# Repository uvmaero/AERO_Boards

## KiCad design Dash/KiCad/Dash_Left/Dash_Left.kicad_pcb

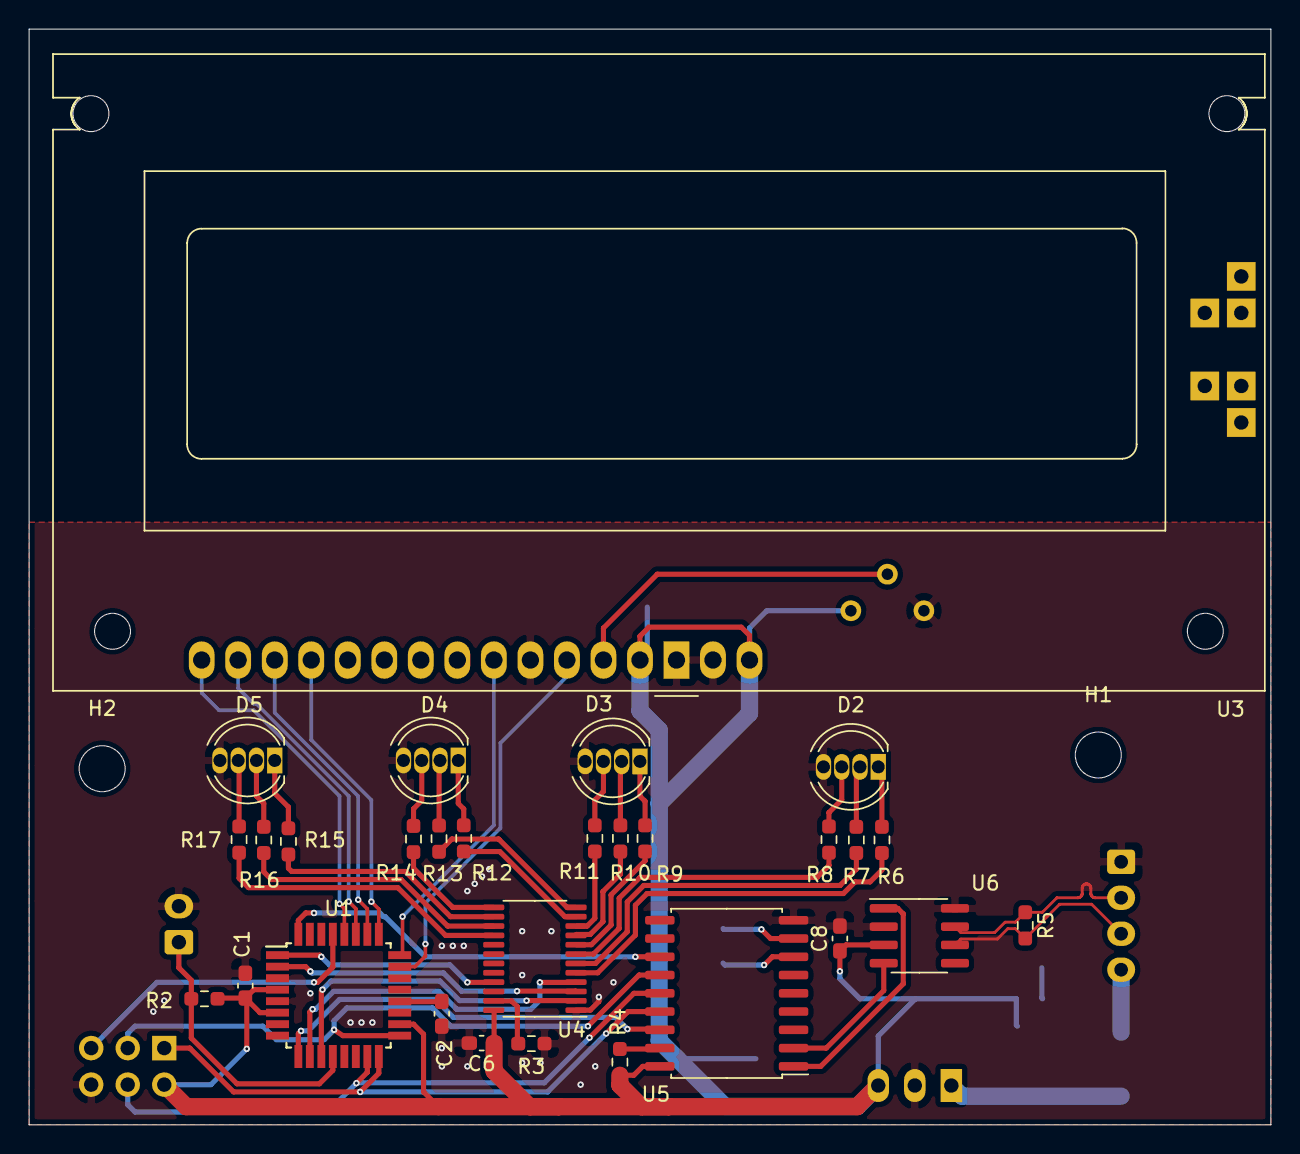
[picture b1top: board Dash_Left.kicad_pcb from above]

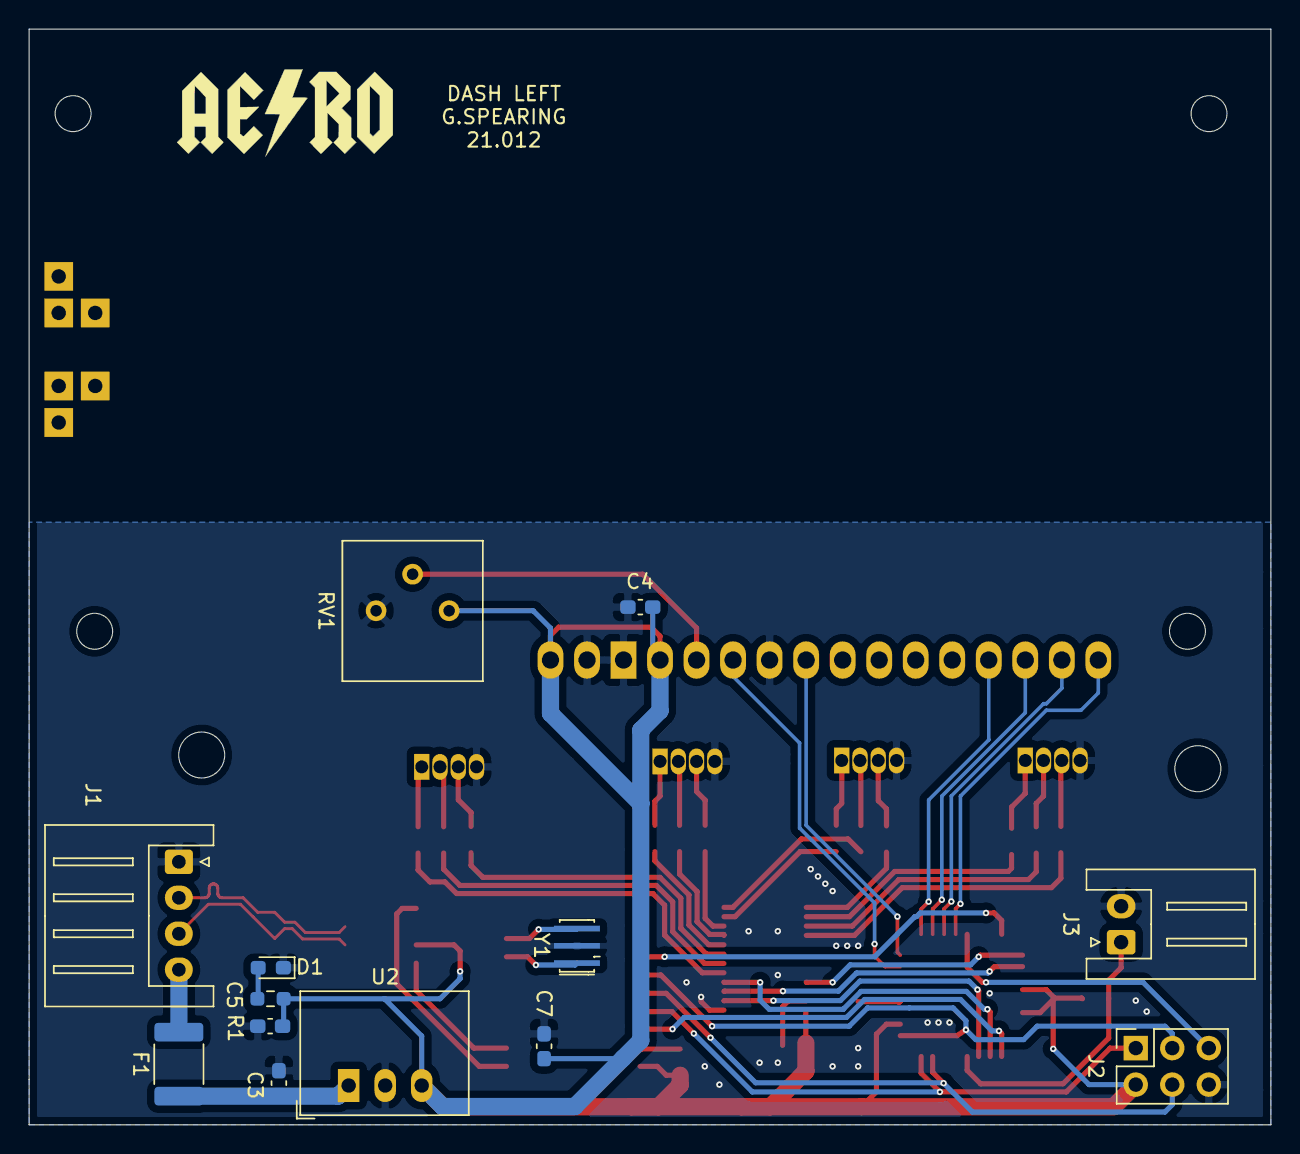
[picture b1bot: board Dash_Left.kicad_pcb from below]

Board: 2 copper layers, 86.4 x 76.2 mm, 44 parts (13 on the bottom side), 56 nets.

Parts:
C1, C2, C4, C6, C7, C8: 0.1u; C_0603_1608Metric_Pad1.08x0.95mm_HandSolder
C3: 1u; C_0603_1608Metric_Pad1.08x0.95mm_HandSolder
C5: 10u; C_0603_1608Metric_Pad1.08x0.95mm_HandSolder
D1: LED; LED_0603_1608Metric_Pad1.05x0.95mm_HandSolder
D2, D3, D4, D5: LED_RGBA; LED_D5.0mm-4_RGB
F1: MF-MSMF050; Fuse_1812_4532Metric_Pad1.30x3.40mm_HandSolder
H1, H2: MountingHole; MountingHole_3.2mm_M3
J1: Conn_01x04; JST_XH_S4B-XH-A_1x04_P2.50mm_Horizontal
J2: Conn_02x03_Odd_Even; PinSocket_2x03_P2.54mm_Vertical
J3: Conn_01x02; JST_XH_S2B-XH-A_1x02_P2.50mm_Horizontal
R1, R6, R7, R8, R9, R10, R11, R12, R13, R14, R15, R16, R17: 330; R_0603_1608Metric_Pad0.98x0.95mm_HandSolder
R2, R4: 10K; R_0603_1608Metric_Pad0.98x0.95mm_HandSolder
R3: 1K; R_0603_1608Metric_Pad0.98x0.95mm_HandSolder
R5: 120; R_0603_1608Metric_Pad0.98x0.95mm_HandSolder
RV1: 10K TRIM; Potentiometer_Bourns_3386P_Vertical
U1: ATmega328P-AU; TQFP-32_7x7mm_P0.8mm
U2: R-785.0-1.0; Converter_DCDC_RECOM_R-78E-0.5_THT
U3: RC1602A
U4: STP16CP05; TSSOP-24_4.4x7.8mm_P0.65mm
U5: MCP2515-xSO; SOIC-18W_7.5x11.6mm_P1.27mm
U6: MCP2551-I-SN; SOIC-8_3.9x4.9mm_P1.27mm
Y1: 16MHz; Resonator_SMD_muRata_CSTxExxV-3Pin_3.0x1.1mm_HandSoldering

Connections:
+5V: C1.1, C4.1, C5.1, C6.1, C7.1, C8.1, J2.2, R1.2, R2.1, R4.1, RV1.1, U1.4, U1.6, U1.18, U2.3, U3.2, U3.15, U4.24, U5.18, U6.3
+12V: F1.2, J1.4
/BATT_B: R17.2, U4.16
/BATT_G: R16.2, U4.15
/BATT_R: R15.2, U4.14
/CAN+: J1.2, R5.1, U6.7
/CAN-: J1.3, R5.2, U6.6
/CAN_CS: U1.9, U5.16
/CAN_INT: U1.32, U5.12
/CAN_Interface/RXCAN: U5.2, U6.4
/CAN_Interface/TXCAN: U5.1, U6.1
/LCD_BTN: J3.1, R2.2, U1.12
/LCD_D4: U1.25, U3.11
/LCD_D5: U1.26, U3.12
/LCD_D6: U1.27, U3.13
/LCD_D7: U1.28, U3.14
/LCD_EN: U1.24, U3.6
/LCD_RS: U1.23, U3.4
/LED_CLK: U1.2, U4.3
/LED_LE: U1.10, U4.4
/LED_OE: U1.1, U4.21
/LED_SDI: U1.11, U4.2
/MISO: J2.1, U1.16, U5.15
/MOSI: J2.4, U1.15, U5.14
/RESET: J2.5, U1.29
/SCK: J2.3, U1.17, U5.13
/TEMP_IND1B: R8.2, U4.7
/TEMP_IND1G: R7.2, U4.6
/TEMP_IND1R: R6.2, U4.5
/TEMP_IND2B: R11.2, U4.10
/TEMP_IND2G: R10.2, U4.9
/TEMP_IND2R: R9.2, U4.8
/TEMP_IND3B: R14.2, U4.13
/TEMP_IND3G: R13.2, U4.12
/TEMP_IND3R: R12.2, U4.11
GND: C1.2, C2.2, C3.2, C4.2, C5.2, C6.2, C7.2, C8.2, D1.1, D2.4, D3.4, D4.4, D5.4, J1.1, J2.6, J3.2, R3.2, RV1.3, U1.3, U1.5, U1.21, U2.2, U3.1, U3.5, U3.16, U4.1, U5.9, U6.2, U6.8, Y1.2
unnamed: C2.1, U1.20
unnamed: C3.1, F1.1, U2.1
unnamed: D1.2, R1.1
unnamed: D2.1, R6.1
unnamed: D2.2, R7.1
unnamed: D2.3, R8.1
unnamed: D3.1, R9.1
unnamed: D3.2, R10.1
unnamed: D3.3, R11.1
unnamed: D4.1, R12.1
unnamed: D4.2, R13.1
unnamed: D4.3, R14.1
unnamed: D5.1, R15.1
unnamed: D5.2, R16.1
unnamed: D5.3, R17.1
unnamed: R3.1, U4.23
unnamed: R4.2, U5.17
unnamed: RV1.2, U3.3
unnamed: U5.7, Y1.1
unnamed: U5.8, Y1.3

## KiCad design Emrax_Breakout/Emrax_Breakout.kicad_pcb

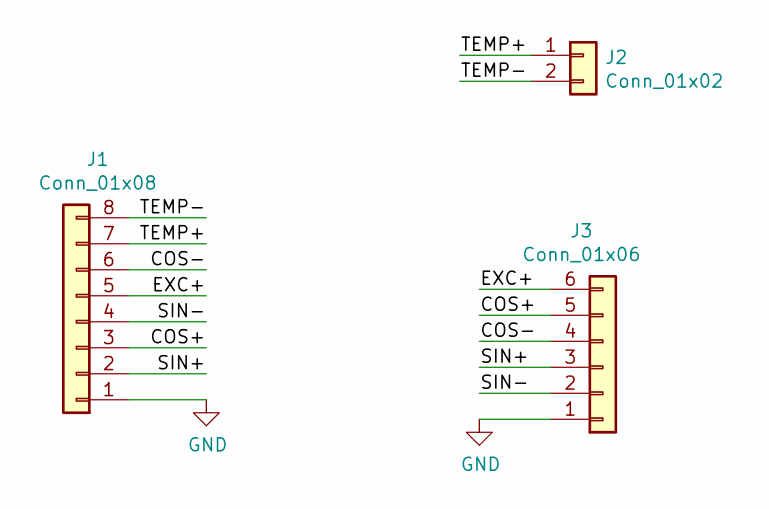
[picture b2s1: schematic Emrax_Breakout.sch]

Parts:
J1: Conn_01x08; TE_1-776276-1_8pin_Vertical
J2: Conn_01x02; JST_PH_B2B-PH-K_1x02_P2.00mm_Vertical
J3: Conn_01x06; JST_PH_B6B-PH-K_1x06_P2.00mm_Vertical

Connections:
/COS+: J1.3, J3.5
/COS-: J1.6, J3.4
/EXC+: J1.5, J3.6
/SIN+: J1.2, J3.3
/SIN-: J1.4, J3.2
/TEMP+: J1.7, J2.1
/TEMP-: J1.8, J2.2
GND: J1.1, J3.1

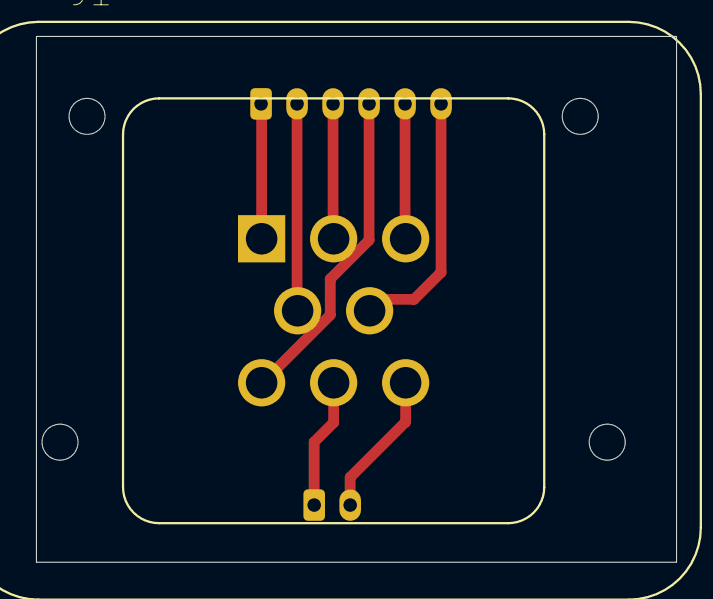
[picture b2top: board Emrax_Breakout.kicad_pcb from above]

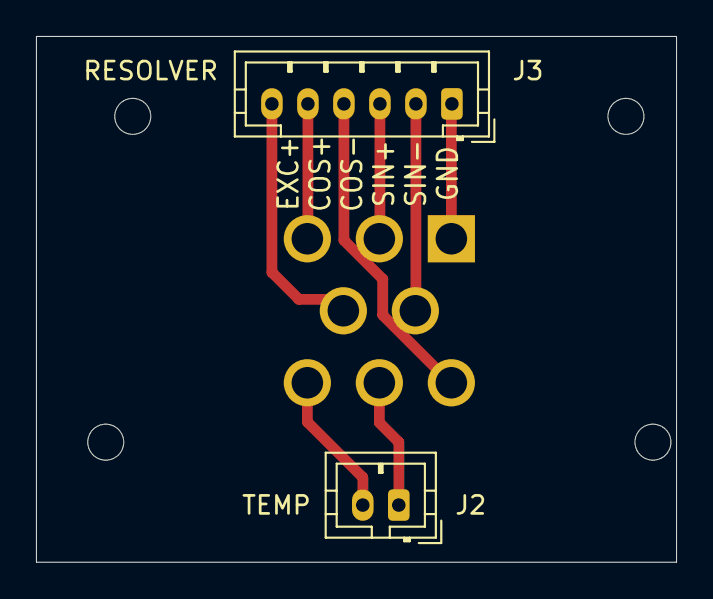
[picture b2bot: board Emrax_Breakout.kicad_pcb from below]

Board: 2 copper layers, 35.6 x 29.2 mm, 3 parts (2 on the bottom side), 8 nets.

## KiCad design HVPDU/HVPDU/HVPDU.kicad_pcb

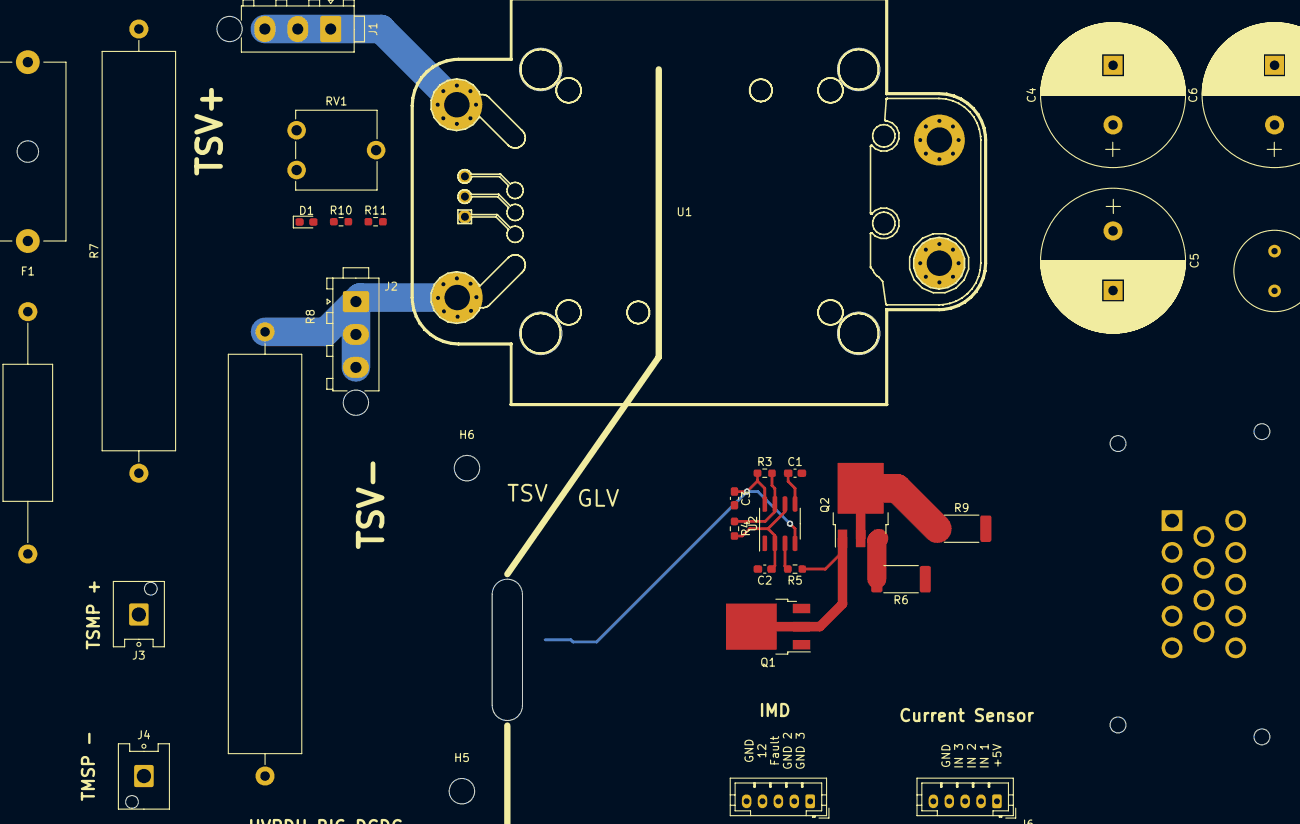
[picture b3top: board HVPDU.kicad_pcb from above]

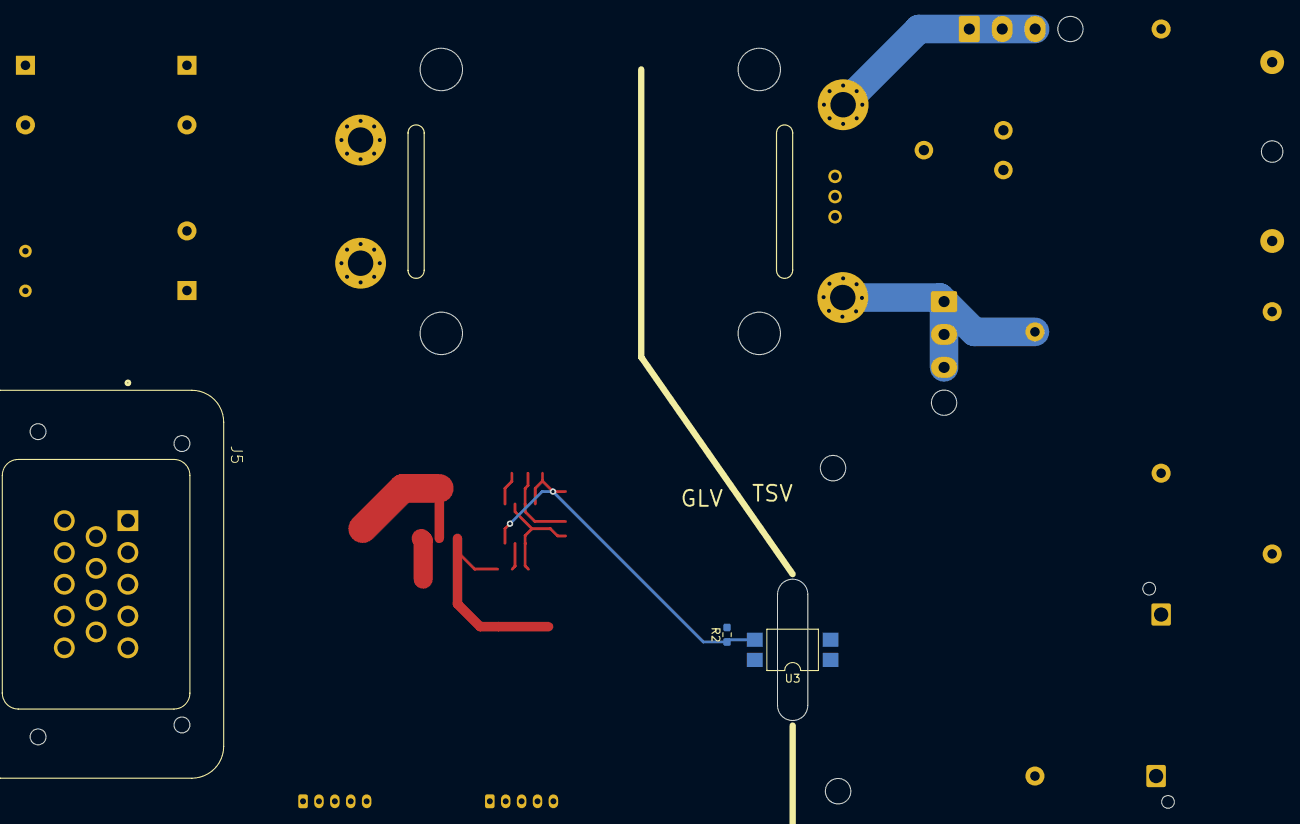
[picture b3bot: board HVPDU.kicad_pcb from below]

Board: 2 copper layers, 35 parts (3 on the bottom side), 29 nets.

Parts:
C1, C3: 0.1u; C_0603_1608Metric_Pad1.08x0.95mm_HandSolder
C2: 1u; C_0603_1608Metric_Pad1.08x0.95mm_HandSolder
C4, C5: 330uF 25V; CAP_18x25_NICH
C6: 47uF 25V; CAP_18x25_NICH
C7: 0.1uF 50v; C_Radial_D10.0mm_H12.5mm_P5.00mm
D1: LED; LED_0603_1608Metric_Pad1.05x0.95mm_HandSolder
F1: 0ADK-2.5A; Fuseholder_Cylinder-5x20mm_Schurter_0031_8201_Horizontal_Op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
H5, H6: M3; MountingHole_3.2mm_M3
J1, J2: TE_Connector; TE_MATE-N-LOK_1-770870-x_1x03_P4.14mm_Vertical
J3, J4: DF22; Hirose_DF63M-1P-3.96DSA_1x01_P3.96mm_Vertical
J5: Conn_01x14; TE_1-776262-1_14pin_Vertical
J6, J7: Conn_01x05; JST_PH_B5B-PH-K_1x05_P2.00mm_Vertical
Q1, Q2: 040N03LG; TO-252-3_TabPin2
R1: 39k; R_Axial_DIN0617_L17.0mm_D6.0mm_P30.48mm_Horizontal
R2, R5: 10k; R_0603_1608Metric_Pad0.98x0.95mm_HandSolder
R3: 100k; R_0603_1608Metric_Pad0.98x0.95mm_HandSolder
R4: 235k; R_0603_1608Metric_Pad0.98x0.95mm_HandSolder
R6: 0.75; R_2512_6332Metric_Pad1.40x3.35mm_HandSolder
R7, R8: 10k; R_Axial_Power_L50.0mm_W9.0mm_P55.88mm
R9: 1.0; R_2512_6332Metric_Pad1.40x3.35mm_HandSolder
R10, R11: R; R_0603_1608Metric_Pad0.98x0.95mm_HandSolder
RV1: R_POT_TRIM; Potentiometer_ACP_CA9-V10_Vertical
U1: Vicor_AERO; vicor-socket
U2: LM555; SOIC-8_3.9x4.9mm_P1.27mm
U3: LTV-817S; SMDIP-4_W9.53mm

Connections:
+5V: J5.4, J6.1
+12V: J5.1, J5.2, J7.2, RV1.1
/+DCDC_OUT: C4.1, C5.1, C6.1, C7.1, J5.9, J5.10, U1.8, U3.4
/FT: R11.2, U1.4
/Fault_IND: J5.3, J7.5
/GND_Chassis: J5.11, J7.4
/GND_Electric: J5.12, J7.1
/INPUT1: J5.5, J6.2
/INPUT2: J5.6, J6.3
/Input3: J5.7, J6.4
/TR: RV1.2, U1.2
/TSAL_TSV+: F1.1, R1.2
/TSAL_on_HVPDU/555_OUT: R5.2, U2.3
/TSAL_on_HVPDU/pass: C2.1, R4.2, U2.2, U2.6
/TSV+: F1.2, J1.1, J1.2, J1.3, R7.2, U1.1
/TSV+_TSMP: J3.1, R7.1
/TSV-: J2.1, J2.2, J2.3, R8.2, U1.5, U3.2
/TSV-_TSMP: J4.1, R8.1
GND: C1.2, C2.2, C3.2, C4.2, C5.2, C6.2, C7.2, J5.13, J5.14, J7.3, Q1.3, R2.2, R6.1, U1.9, U2.1
GNDREF: J5.8, J6.5
unnamed: C1.1, U2.5
unnamed: D1.1, R10.1
unnamed: D1.2, R10.2, R11.1
unnamed: Q1.1, Q2.3, R6.2
unnamed: Q1.2, Q2.1, R5.1
unnamed: Q2.2, R9.1
unnamed: R1.1, U3.1
unnamed: R3.2, R4.1, U2.7
VCC: C3.1, R2.1, R3.1, U2.4, U2.8, U3.3

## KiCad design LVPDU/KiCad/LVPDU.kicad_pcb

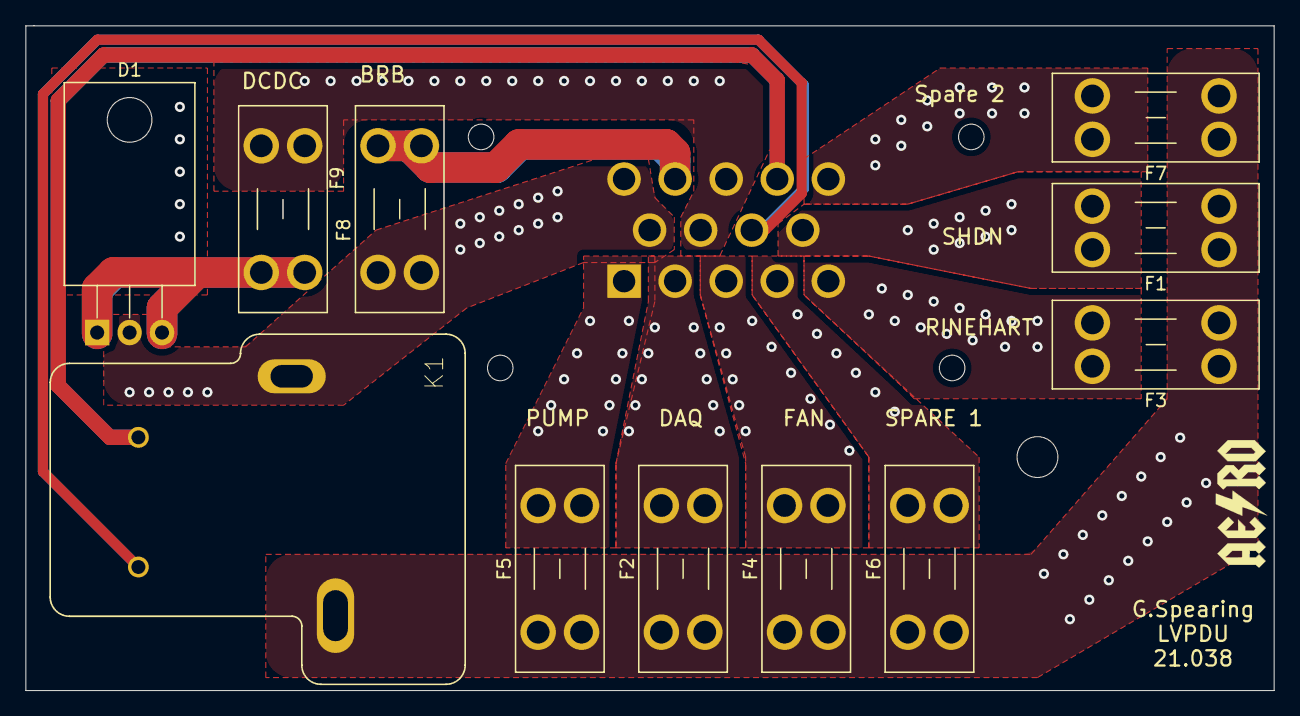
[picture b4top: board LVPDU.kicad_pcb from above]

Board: 2 copper layers, 97.8 x 52.1 mm, 13 parts (1 on the bottom side), 14 nets.

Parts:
D1: D_Schottky_AKA; TO-220-3_Horizontal_TabDown
F1, F2, F3, F4, F5, F6, F7, F8, F9: 3568 Mini Blade; Fuseholder_Blade_Mini_Keystone_3568
H1: MountingHole; MountingHole_3.2mm_M3
J1: Conn_01x14; TE_1-776262-1_14pin_Vertical
K1: T9VV1K15-12S; RELAY_T9VV1K15-12S

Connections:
+12V: F1.1, F2.1, F3.1, F4.1, F5.1, F6.1, F7.1, K1.4
/12V_OUT_1: F6.2, J1.4
/12V_OUT_2: F7.2, J1.14
/BATT_IN: D1.2, F8.2, J1.6, J1.10, K1.3
/DAQ: F2.2, J1.2
/DCDC_Fused: D1.1, D1.3, F9.2
/DCDC_IN: F9.1, J1.7, J1.12
/FROM_BRB: J1.13, K1.2
/PUMP: F5.2, J1.1
/RADIATOR: F4.2, J1.3
/RINEHART: F3.2, J1.5
/SHUTDOWN_OUT: F1.2, J1.9
/TO_BRB: F8.1, J1.11
GND: J1.8, K1.1
